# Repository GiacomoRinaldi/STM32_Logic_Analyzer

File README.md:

# STM32 Logic Analyzer

A versatile 4-channel logic analyzer built around the STM32F103 microcontroller, designed for analyzing digital communication protocols including I2C, SPI, and UART.

## Overview

This project implements a dual-mode logic analyzer capable of capturing and analyzing digital signals:

- **Polling Mode**: Continuously samples all 4 channels at regular intervals using DWT (Data Watchpoint and Trace) cycle counting for precise timing
- **Interrupt Mode**: Event-driven sampling that captures signal transitions (rising/falling edges) with timestamps, optimized for analyzing communication protocols

The device streams captured data over USB and includes Python scripts for visualization and protocol decoding.

### Circuit Shematic
<div align="center">
  
</div>

### PCB Layout
<div align="center">
  
</div>

### Device in Use
<table>
  <tr>
    <td></td>
    <td></td>
  </tr>
  <tr>
    <td align="center">SPI Wiring</td>
    <td align="center">Example Trace</td>
  </tr>
</table>

### Current Work - 2nd Iteration of Device
<table>
  <tr>
    <td></td>
    <td></td>
  </tr>
  <tr>
    <td align="center">V2.0 Circuit Schematic</td>
    <td align="center">V2.0 PCB</td>
  </tr>
</table>

## Features

- **4-Channel Digital Input**: Simultaneous monitoring of up to 4 digital signals
- **Dual Operating Modes**:
  - Polling mode for continuous sampling
  - Interrupt mode for edge-triggered event capture
- **Protocol Support**: Built-in decoding for I2C, SPI, and UART communication protocols
- **USB Connectivity**: Real-time data streaming via USB CDC (Virtual COM Port)
- **Python Integration**: Comprehensive plotting and decoding scripts for data analysis
- **High-Resolution Timing**: Utilizes STM32's DWT cycle counter and cascaded timers for precise timestamping
- **Efficient Data Handling**: Double-buffered data collection to minimize sample loss

## Hardware Specifications

- **MCU**: STM32F103 (72MHz ARM Cortex-M3)
- **Input Channels**: 4 channels (CH1-CH4) on pins PB4-PB7
- **Sample Rate**: Variable depending on mode
- **Data Interface**: USB 2.0 Full Speed
- **Power**: USB-powered
- **Input Voltage**: 3.3V logic levels

## Setup Instructions

### PCB Assembly
1. Order the PCB from JLCPCB using the production files in the `pcb_production_files/` folder
2. Solder components according to the provided schematic
3. Ensure proper USB connector installation for data communication

### Firmware Installation

**Option 1: SWD Programming**
1. Connect an ST-Link or compatible SWD programmer to the SWDIO and SCLK pins on the STM32F103
2. Flash the appropriate firmware binary (polling or interrupt mode)
3. Reset the device

**Option 2: DFU Bootloader**
1. Upload the bootloader from the `misc/` folder using SWD
2. Connect the device via USB
3. Use DFU utilities to upload the main firmware over USB

### Software Setup
1. Install Python dependencies for the analysis scripts
2. Connect the logic analyzer to your computer via USB
3. Connect target device signals to channels CH1-CH4
4. Run the Python plotting script to capture and visualize data
5. Use the decoding script to analyze communication protocols

### Usage Workflow
```bash
# 1. Capture data
python polling_plotter.py

# 2. Decode protocols
python polling_decoder.py
```

## Operating Modes

### Polling Mode
- Continuously samples all 4 channels at maximum rate
- Provides complete signal history with regular time intervals
- Best for analyzing continuous signals or unknown protocols
- Uses DWT cycle counter for precise timing
- Double-buffered operation prevents data loss during USB transmission

### Interrupt Mode
- Event-driven capture on signal transitions
- Efficient for sparse signals and protocol analysis
- Captures rising and falling edges with precise timestamps
- Uses cascaded TIM2/TIM3 timers for extended timing range
- Automatically shuts down after ~1.74 minutes to prevent timer overflow

## Data Format

### Polling Mode
```c
typedef struct {
    uint32_t timestamp;  // DWT cycle count
    uint8_t value;       // 4-bit channel states (PB4-PB7)
} Sample;
```

### Interrupt Mode
```
32-bit data format:
- Bit 31: Edge type (1=rising, 0=falling)
- Bits 30-29: Channel number (0-3)
- Bits 28-0: Timestamp (29-bit timer value)
```

## Python Scripts

The included Python scripts provide:
- **Data Visualization**: Real-time plotting of captured signals
- **Protocol Decoding**: Automatic analysis of I2C, SPI, and UART communications
- **Export Capabilities**: Save captured data in various formats
- **Customizable Analysis**: Modify scripts for specific protocols or requirements

## Development Plans

- **Hardware Upgrades**:
  - Migrate to higher-performance STM32 module with increased clock speed
  - Add external SRAM for larger capture buffers
  - Implement DMA-based USB transfers for improved throughput

- **Software Enhancements**:
  - Real-time protocol decoding during capture
  - Enhanced user interface for data visualization
  - Trigger functionality for complex capture scenarios

- **Performance Improvements**:
  - Optimize sampling rates and buffer management
  - Implement compression for longer capture sessions
  - Add hardware-based triggering capabilities

## Contributing

Contributions are welcome! Please feel free to submit issues, feature requests, or pull requests to improve the logic analyzer's functionality. This is an ongoing project that I plan to keep enhancing over time.

## Troubleshooting

- **Device not recognized**: Ensure USB drivers are properly installed
- **No data capture**: Verify connections to CH1-CH4 pins and signal voltage levels
- **Timing issues**: Check that target device and logic analyzer share common ground
- **Buffer overflow**: Reduce sampling rate or increase USB transfer frequency

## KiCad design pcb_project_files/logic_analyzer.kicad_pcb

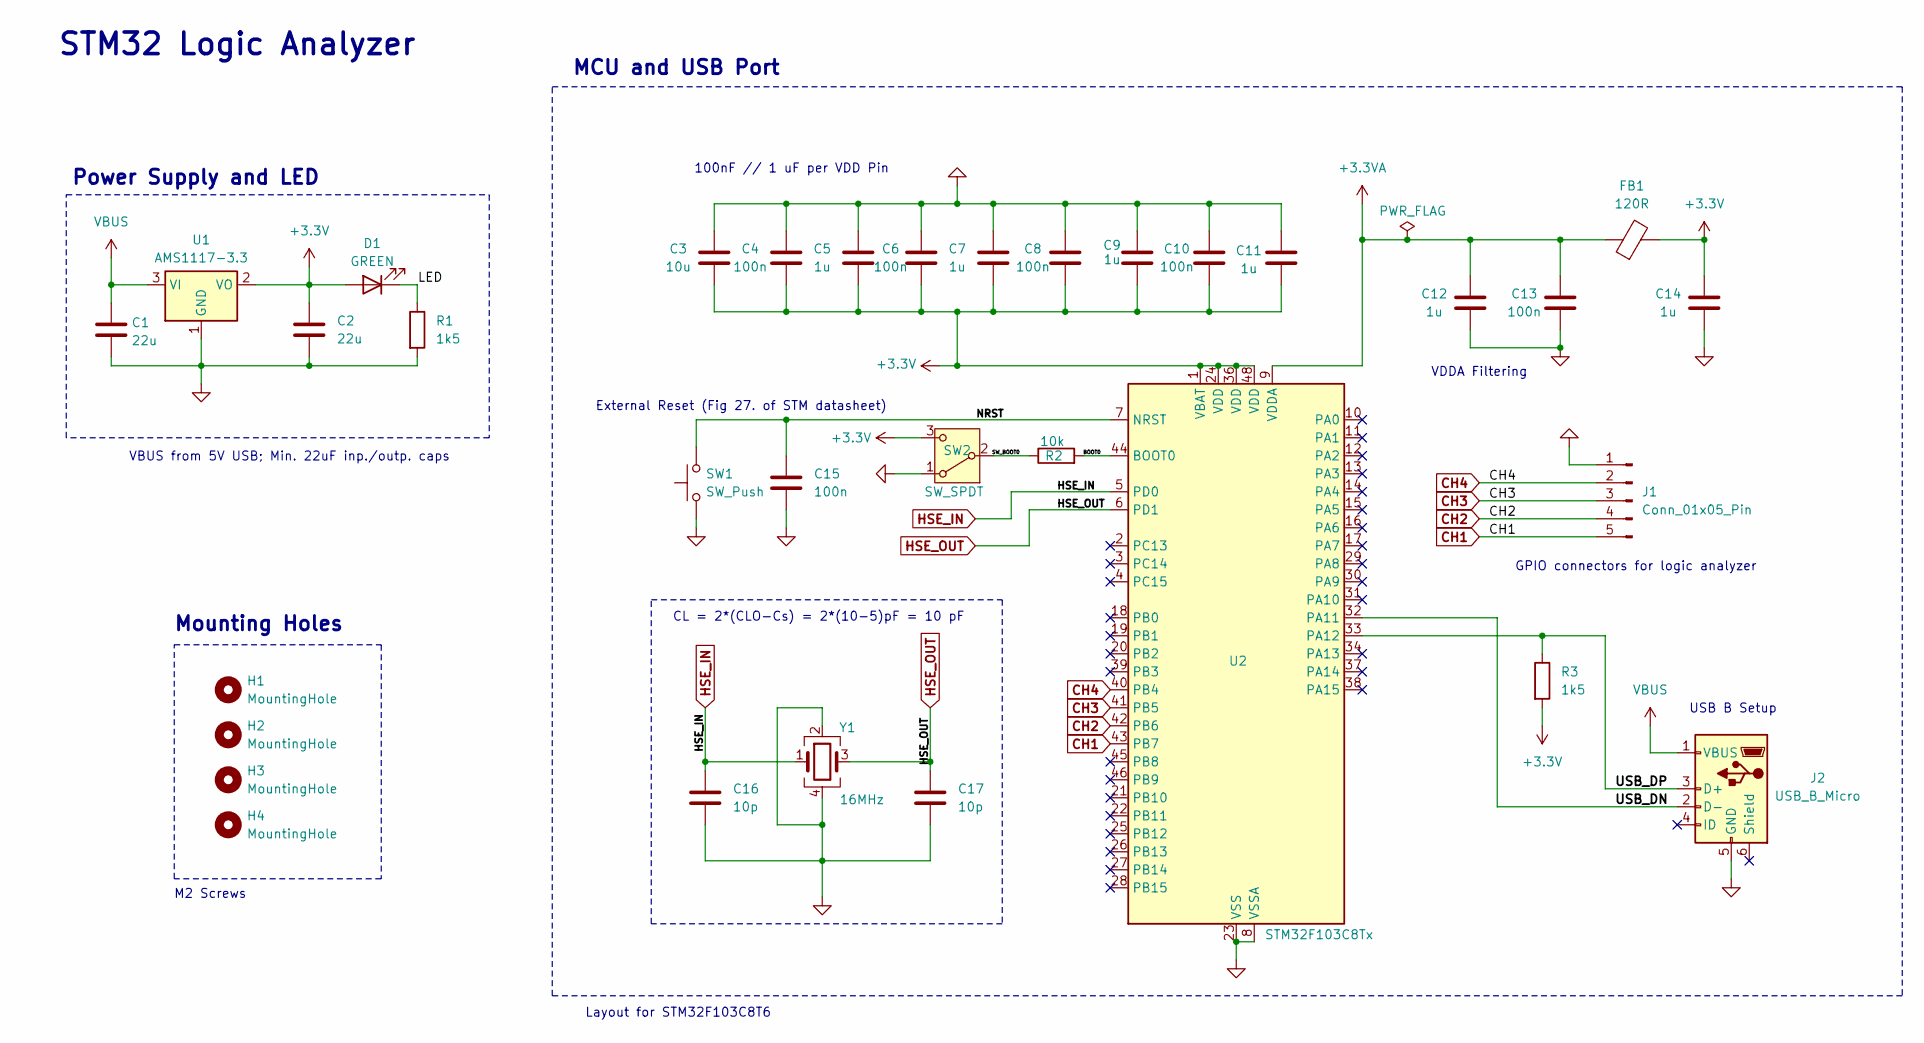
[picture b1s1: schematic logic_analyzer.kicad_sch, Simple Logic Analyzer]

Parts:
C1, C2: 22u; C_0805_2012Metric
C3: 10u; C_0603_1608Metric
C4, C6, C8, C10, C13, C15: 100n; C_0402_1005Metric
C5, C7, C9, C11, C12, C14: 1u; C_0402_1005Metric
C16, C17: 10p; C_0402_1005Metric
D1: GREEN; LED_0603_1608Metric
FB1: 120R; L_0603_1608Metric
H1, H2, H3, H4: MountingHole; MountingHole_2.2mm_M2
J1: Conn_01x05_Pin; PinSocket_1x05_P2.00mm_Horizontal
J2: USB_B_Micro; USB_Micro-B_Wuerth_629105150521
R1, R3: 1k5; R_0402_1005Metric
R2: 10k; R_0402_1005Metric
SW1: SW_Push; SW_SPST_TL3342
SW2: SW_SPDT; SW_SPDT_PCM12
U1: AMS1117-3.3; SOT-223-3_TabPin2
U2: STM32F103C8Tx; LQFP-48_7x7mm_P0.5mm
Y1: 16MHz; Crystal_SMD_3225-4Pin_3.2x2.5mm

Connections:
+3.3V: C2.1, C3.1, C4.1, C5.1, C6.1, C7.1, C8.1, C9.1, C10.1, C11.1, C14.2, D1.2 (A), FB1.2, R3.2, SW2.3 (C), U1.2 (VO), U2.1 (VBAT), U2.24 (VDD), U2.36 (VDD), U2.48 (VDD)
+3.3VA: C12.2, C13.2, FB1.1, U2.9 (VDDA)
/BOOT0: R2.2, U2.44 (BOOT0)
/LED: D1.1 (K), R1.1
/NRST: C15.1, SW1.2, U2.7 (NRST)
/SW_BOOT0: R2.1, SW2.2 (B)
/USB_DN: J2.2 (D-), U2.32 (PA11)
/USB_DP: J2.3 (D+), R3.1, U2.33 (PA12)
CH1: J1.5, U2.43 (PB7)
CH2: J1.4, U2.42 (PB6)
CH3: J1.3, U2.41 (PB5)
CH4: J1.2, U2.40 (PB4)
GND: C1.2, C2.2, C3.2, C4.2, C5.2, C6.2, C7.2, C8.2, C9.2, C10.2, C11.2, C12.1, C13.1, C14.1, C15.2, C16.2, C17.2, J1.1, J2.5 (GND), R1.2, SW1.1, SW2.1 (A), U1.1 (GND), U2.8 (VSSA), U2.23 (VSS), U2.35 (VSS), U2.47 (VSS), Y1.2, Y1.4
HSE_IN: C16.1, U2.5 (PD0), Y1.1
HSE_OUT: C17.1, U2.6 (PD1), Y1.3
VBUS: C1.1, J2.1 (VBUS), U1.3 (VI)

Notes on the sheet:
VBUS from 5V USB; Min. 22uF inp./outp. caps
100nF // 1 uF per VDD Pin
USB B Setup
External Reset (Fig 27. of STM datasheet)
M2 Screws
Power Supply and LED
CL = 2*(CLO-Cs) = 2*(10-5)pF = 10 pF
Layout for STM32F103C8T6
VDDA Filtering
Mounting Holes
GPIO connectors for logic analyzer
MCU and USB Port
STM32 Logic Analyzer

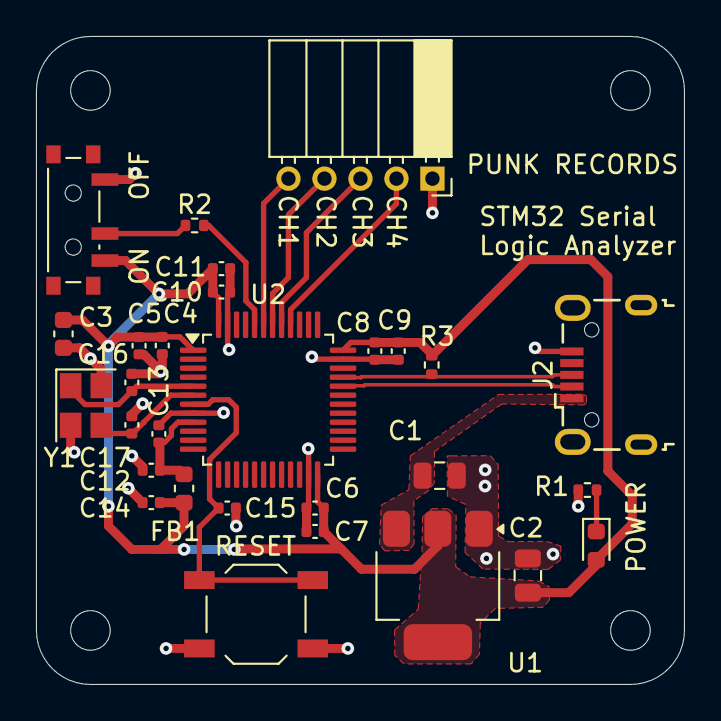
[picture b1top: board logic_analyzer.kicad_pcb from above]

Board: 2 copper layers, 36.0 x 36.0 mm, 33 parts (0 on the bottom side), 16 nets.

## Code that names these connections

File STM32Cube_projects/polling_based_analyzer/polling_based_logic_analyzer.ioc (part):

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Mcu.Name=STM32F103C(8-B)Tx
Mcu.Package=LQFP48
Mcu.UserName=STM32F103C8Tx
PA11.GPIOParameters=GPIO_Label
PA11.GPIO_Label=USB-DN
PA11.Mode=Device
PA11.Signal=USB_DM
PA12.GPIOParameters=GPIO_Label
PA12.GPIO_Label=USB-DP
PA12.Mode=Device
PA12.Signal=USB_DP
PB4.GPIOParameters=GPIO_Label
PB4.GPIO_Label=CH4
PB4.Signal=GPIO_Input
PB5.GPIOParameters=GPIO_Label
PB5.GPIO_Label=CH3
PB5.Signal=GPIO_Input
PB6.GPIOParameters=GPIO_Label
PB6.GPIO_Label=CH2
PB6.Signal=GPIO_Input
PB7.GPIOParameters=GPIO_Label
PB7.GPIO_Label=CH1
PB7.Signal=GPIO_Input
PD0-OSC_IN.GPIOParameters=GPIO_Label
PD0-OSC_IN.GPIO_Label=HSE_IN
PD0-OSC_IN.Mode=HSE-External-Oscillator
PD0-OSC_IN.Signal=RCC_OSC_IN
PD1-OSC_OUT.GPIOParameters=GPIO_Label
PD1-OSC_OUT.GPIO_Label=HSE_OUT
PD1-OSC_OUT.Mode=HSE-External-Oscillator
PD1-OSC_OUT.Signal=RCC_OSC_OUT
RCC.SYSCLKFreq_VALUE=72000000
RCC.SYSCLKSource=RCC_SYSCLKSOURCE_PLLCLK
board=custom

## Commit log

2025-07-03 adding serial decoder file v0.1
2025-07-08 adding bootloader binary
2025-07-12 adding 16MHz bootloader
2025-07-12 adding PCB project and production files
2025-07-12 created arduino tester file
2025-07-12 updating python scripts
2025-07-12 trying to get UART up and running
2025-07-12 deleting bitlogging files
2025-07-12 reorganized files
2025-07-16 dumping file changes
2025-07-16 reorganizing files
2025-07-16 orgznied even more files
2025-07-17 adding polling_based scripts
2025-07-17 improved README
2025-07-17 adjusting picture sizes in README
2025-07-27 beginning version 2
2025-08-03 adding photos for V2
2025-08-03 updating current work section
